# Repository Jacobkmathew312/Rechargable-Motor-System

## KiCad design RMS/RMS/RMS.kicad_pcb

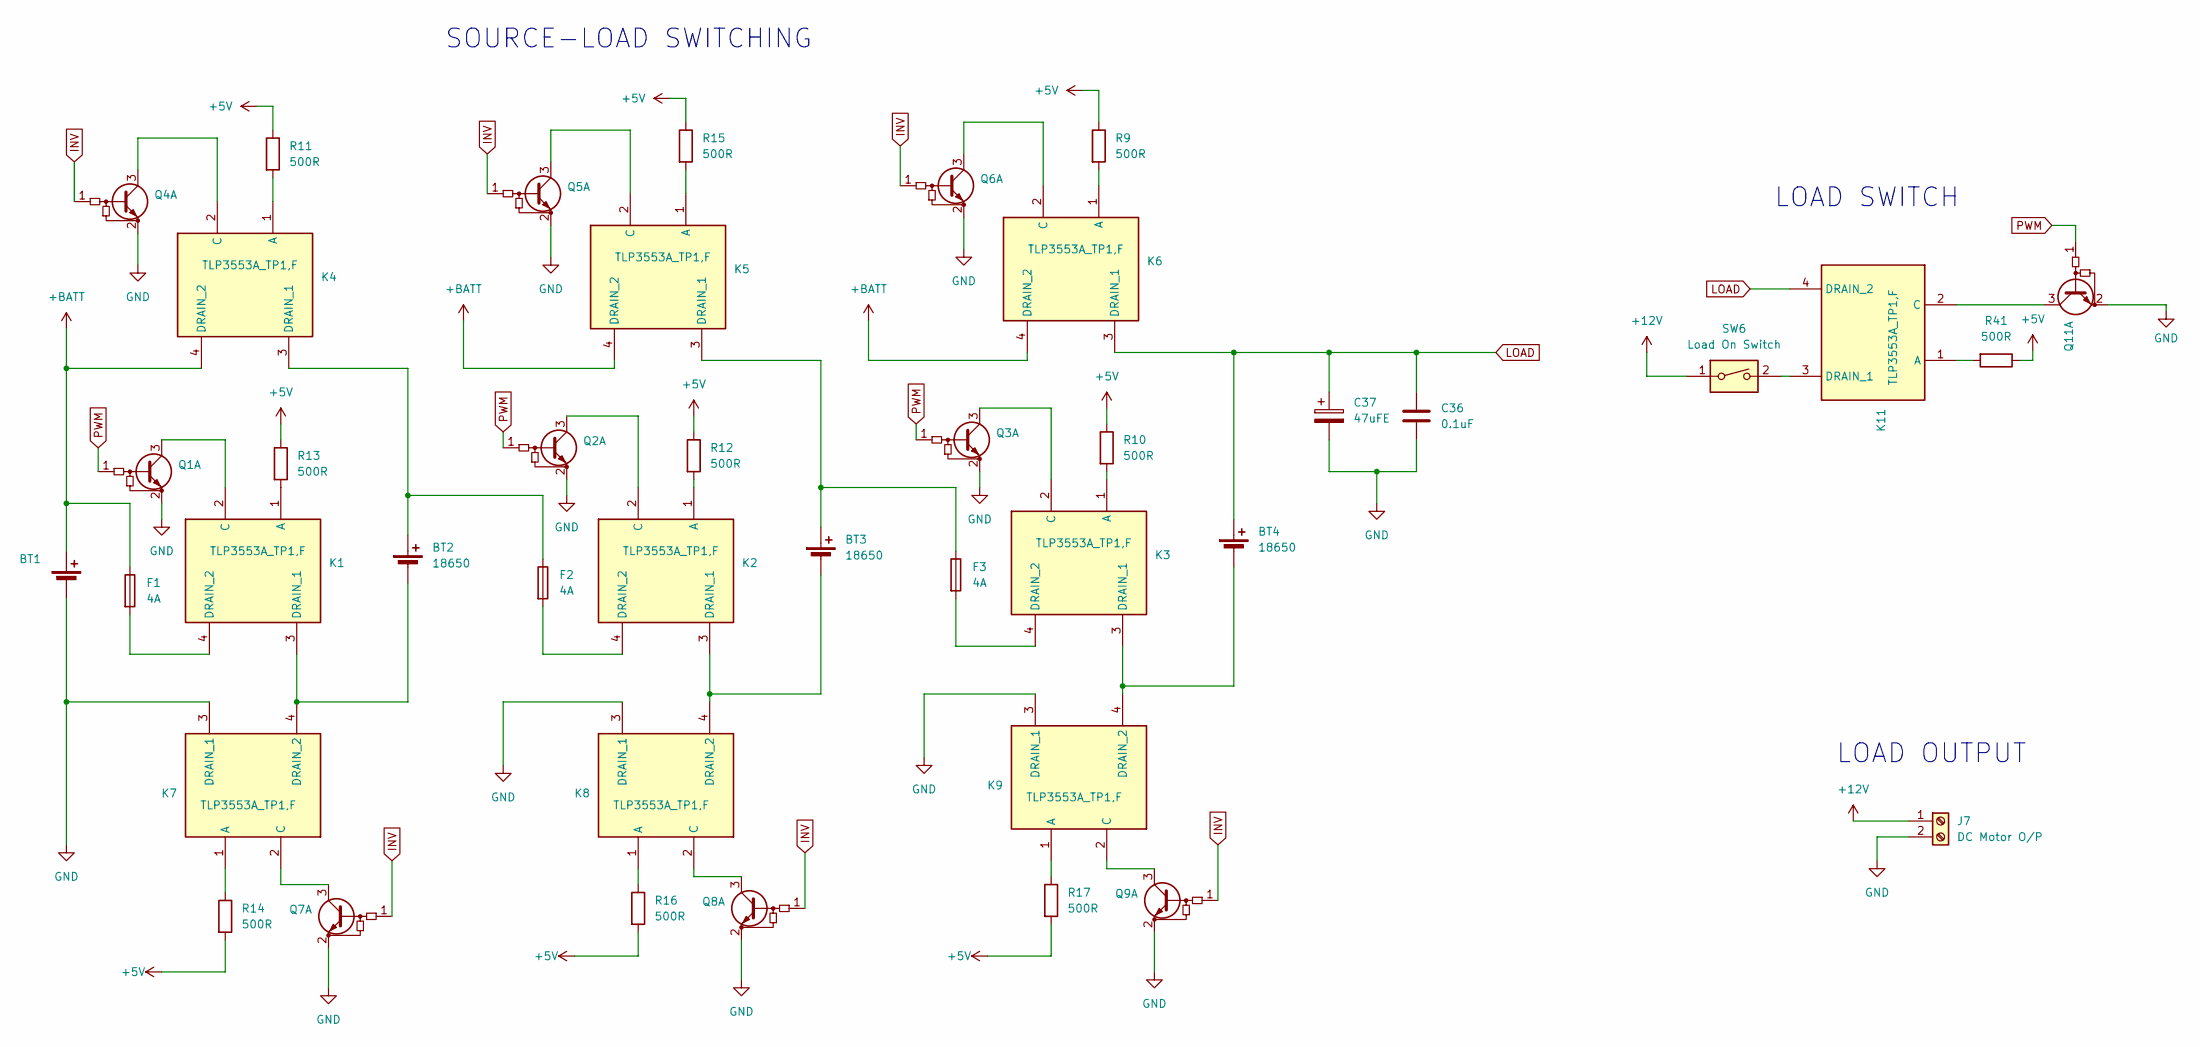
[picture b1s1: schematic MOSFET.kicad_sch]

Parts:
BT1, BT2, BT3, BT4: 18650; battery pad
C36: 0.1uF; C_0603_1608Metric
C37: 47uFE; C_Elec_6.3x5.4
F1, F2, F3: 4A; Fuse_1812_4532Metric
J7: DC Motor O/P; AMASS_XT30U-M_1x02_P5.0mm_Vertical
K1, K2, K3, K4, K5, K6, K7, K8, K9, K11: TLP3553A_TP1,F; SOIC_3553ATP1_F_TOS; Mouser Part Number 757-TLP3543ATP1F
Q1, Q2, Q3, Q4, Q5, Q6, Q7, Q8, Q9, Q11: Q_Dual_NPN_NPN_BRT_E1B1C2E2B2C1; SOT-323_SC-70
R9, R10, R11, R12, R13, R14, R15, R16, R17, R41: 500R; R_0805_2012Metric
SW6: Load On Switch; Push button

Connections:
+5V: R9.1, R10.1, R11.1, R12.1, R13.1, R14.2, R15.1, R16.2, R17.2, R41.1; also elsewhere on the board
+12V: J7.1, SW6.1; also elsewhere on the board
+BATT: BT1.1 (+), F1.1, K4.4 (DRAIN_2), K5.4 (DRAIN_2), K6.4 (DRAIN_2); also elsewhere on the board
INV: Q4.1 (B1), Q5.1 (B1), Q6.1 (B1), Q7.1 (B1), Q8.1 (B1), Q9.1 (B1); also elsewhere on the board
LOAD: BT4.1 (+), C36.1, C37.1, K6.3 (DRAIN_1), K11.4 (DRAIN_2); also elsewhere on the board
unnamed: BT2.1 (+), F2.1, K4.3 (DRAIN_1)
unnamed: BT3.1 (+), F3.1, K5.3 (DRAIN_1)
unnamed: BT3.2 (-), K2.3 (DRAIN_1), K8.4 (DRAIN_2)
unnamed: BT4.2 (-), K3.3 (DRAIN_1), K9.4 (DRAIN_2)
unnamed: K1.1 (A), R13.2
unnamed: K1.2 (C), Q1.3 (C1)
unnamed: F1.2, K1.4 (DRAIN_2)
unnamed: K2.1 (A), R12.2
unnamed: K2.2 (C), Q2.3 (C1)
unnamed: F2.2, K2.4 (DRAIN_2)
unnamed: K3.1 (A), R10.2
unnamed: K3.2 (C), Q3.3 (C1)
unnamed: F3.2, K3.4 (DRAIN_2)
unnamed: K4.2 (C), Q4.3 (C1)
unnamed: K5.1 (A), R15.2
unnamed: K5.2 (C), Q5.3 (C1)
unnamed: K6.1 (A), R9.2
unnamed: K6.2 (C), Q6.3 (C1)
unnamed: K8.1 (A), R16.1
unnamed: K8.2 (C), Q8.3 (C1)
unnamed: K9.1 (A), R17.1
unnamed: K11.1 (A), R41.2
unnamed: K11.2 (C), Q11.3 (C1)
unnamed: K11.3 (DRAIN_1), SW6.2
PWM: Q1.1 (B1), Q2.1 (B1), Q3.1 (B1), Q11.1 (B1); also elsewhere on the board

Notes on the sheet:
LOAD SWITCH
SOURCE-LOAD SWITCHING
LOAD OUTPUT

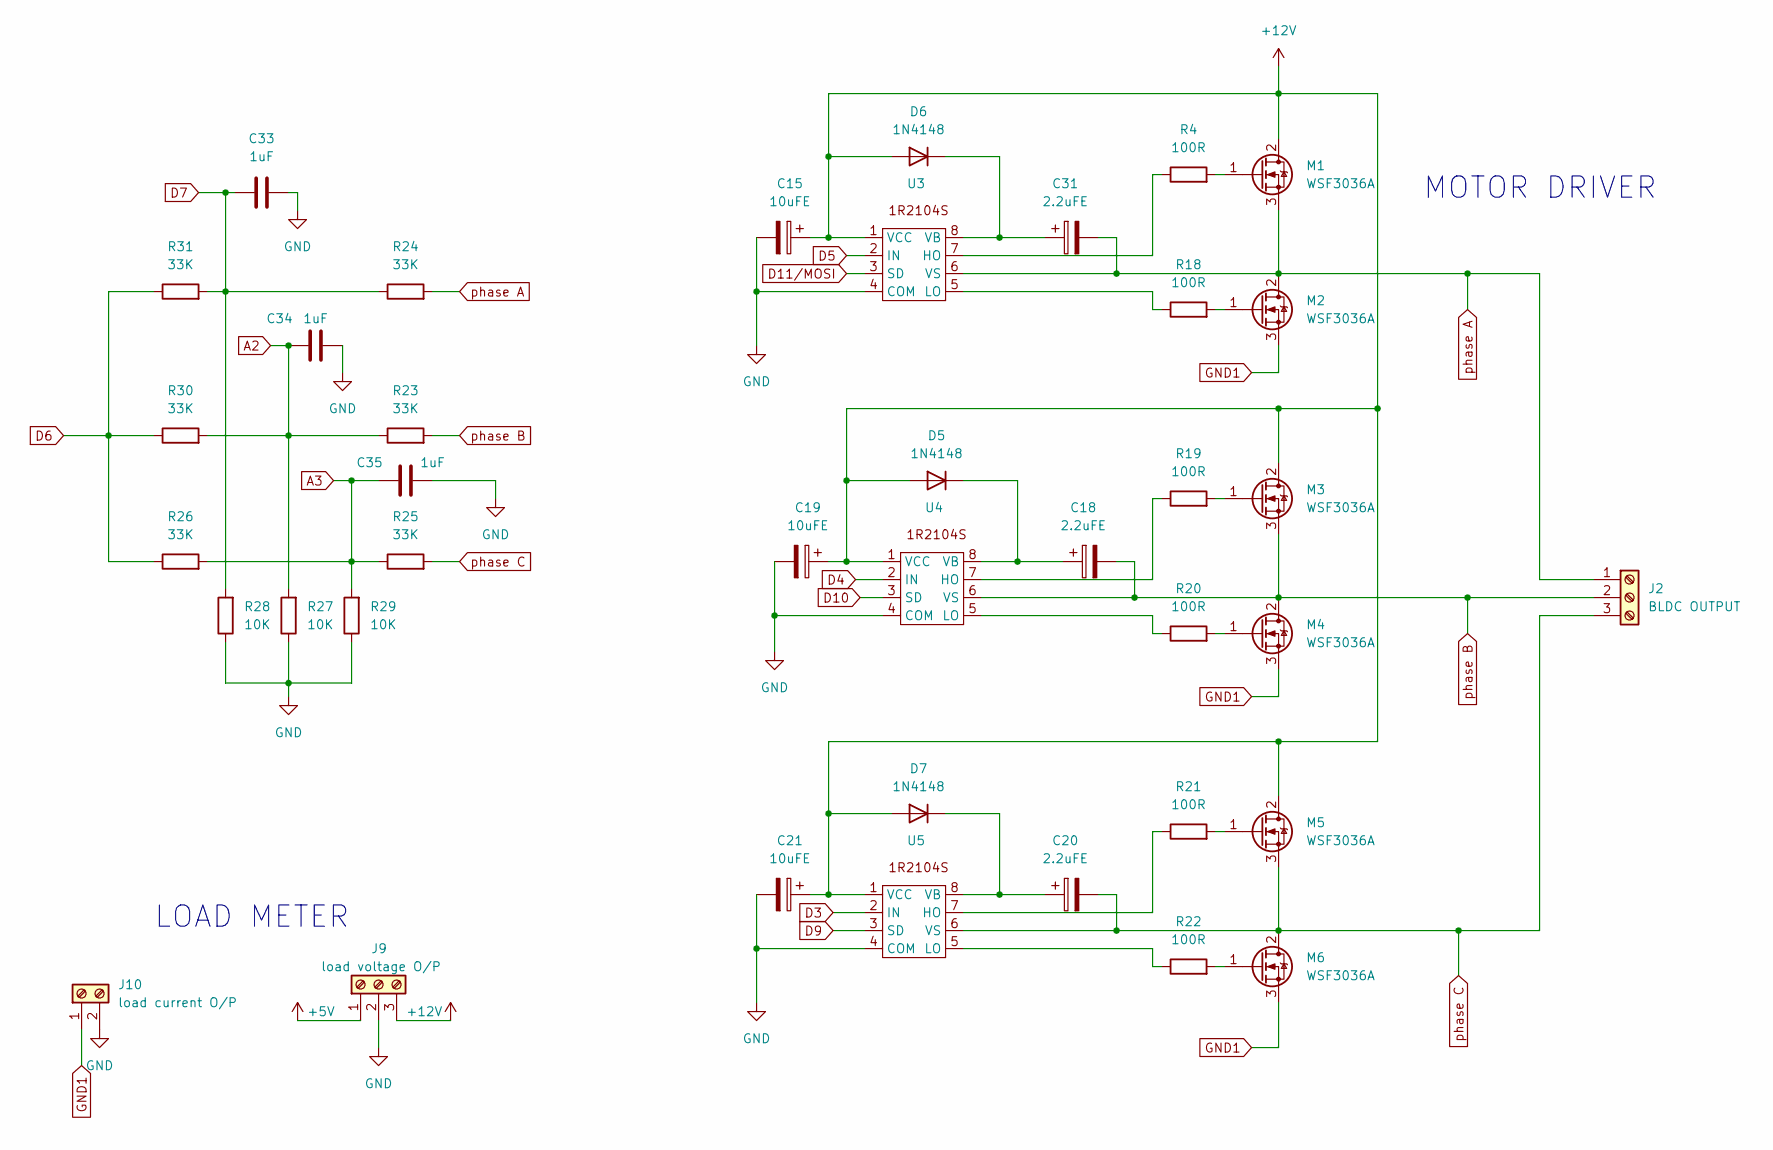
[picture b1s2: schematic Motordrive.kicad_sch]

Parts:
C15, C19, C21: 10uFE; CP_Elec_4x5.4
C18, C20, C31: 2.2uFE; C_Elec_4x5.4
C33, C34, C35: 1uF; C_0603_1608Metric
D5, D6, D7: 1N4148; D_SOD-123
J2: BLDC OUTPUT; BLDC
J9: load voltage O/P; voltage slot
J10: load current O/P; current slot
M1, M2, M3, M4, M5, M6: WSF3036A; TO-252-2
R4, R18, R19, R20, R21, R22: 100R; R_0603_1608Metric
R23, R24, R25, R26, R30, R31: 33K; R_0603_1608Metric
R27, R28, R29: 10K; R_0603_1608Metric
U3, U4, U5: SOIC-8_3.9x4.9mm_P1.27mm

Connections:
+5V: J9.1; also elsewhere on the board
+12V: C15.1, C19.1, C21.1, D5.2 (A), D6.2 (A), D7.2 (A), J9.3, M1.2 (D), M3.2 (D), M5.2 (D), U3.1 (VCC), U4.1 (VCC), U5.1 (VCC); also elsewhere on the board
A2: C34.2, R23.1, R27.2, R30.2; also elsewhere on the board
A3: C35.1, R25.1, R26.2, R29.2; also elsewhere on the board
D3: U5.2 (IN); also elsewhere on the board
D4: U4.2 (IN); also elsewhere on the board
D5: U3.2 (IN); also elsewhere on the board
D6: R26.1, R30.1, R31.1; also elsewhere on the board
D7: C33.1, R24.1, R28.2, R31.2; also elsewhere on the board
D9: U5.3 (SD); also elsewhere on the board
D10: U4.3 (SD); also elsewhere on the board
D11/MOSI: U3.3 (SD); also elsewhere on the board
GND1: J10.1, M2.3 (S), M4.3 (S), M6.3 (S)
unnamed: C18.1, D5.1 (K), U4.8 (VB)
unnamed: C31.1, D6.1 (K), U3.8 (VB)
unnamed: C20.1, D7.1 (K), U5.8 (VB)
unnamed: M1.1 (G), R4.2
unnamed: M2.1 (G), R18.2
unnamed: M3.1 (G), R19.2
unnamed: M4.1 (G), R20.2
unnamed: M5.1 (G), R21.2
unnamed: M6.1 (G), R22.2
unnamed: R4.1, U3.7 (HO)
unnamed: R18.1, U3.5 (LO)
unnamed: R19.1, U4.7 (HO)
unnamed: R20.1, U4.5 (LO)
unnamed: R21.1, U5.7 (HO)
unnamed: R22.1, U5.5 (LO)
phase A: C31.2, J2.1, M1.3 (S), M2.2 (D), R24.2, U3.6 (VS)
phase B: C18.2, J2.2, M3.3 (S), M4.2 (D), R23.2, U4.6 (VS)
phase C: C20.2, J2.3, M5.3 (S), M6.2 (D), R25.2, U5.6 (VS)

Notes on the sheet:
LOAD METER
MOTOR DRIVER

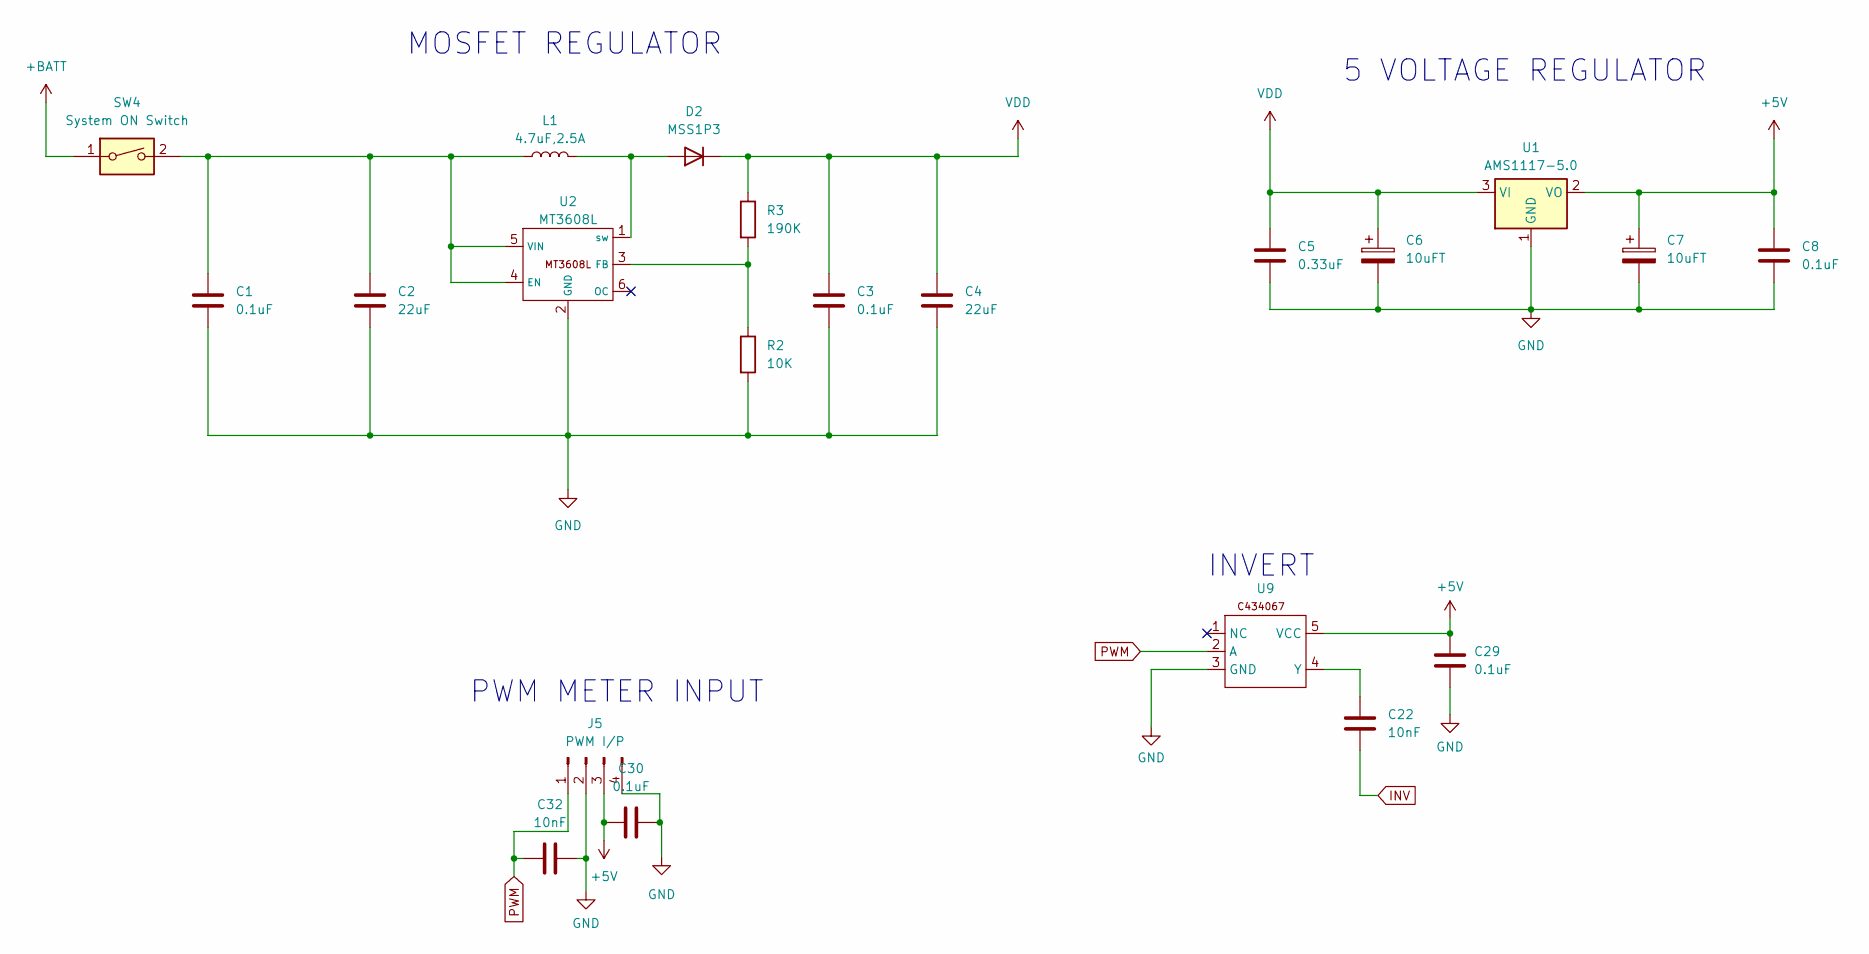
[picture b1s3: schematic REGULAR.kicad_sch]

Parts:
C1, C3, C8, C29, C30: 0.1uF; C_0603_1608Metric
C2, C4: 22uF; C_0603_1608Metric
C5: 0.33uF; C_0603_1608Metric
C6, C7: 10uFT; CP_EIA-3216-10_Kemet-I
C22, C32: 10nF; C_0603_1608Metric
D2: MSS1P3; D_MicroSMP_AK
J5: PWM I/P; PWM
L1: 4.7uF,2.5A; 4.7uH 2.5A
R2: 10K; R_0603_1608Metric
R3: 190K; R_0603_1608Metric
SW4: System ON Switch; Push button
U1: AMS1117-5.0; SOT-223-3_TabPin2
U2: MT3608L; SOT-23-6
U9: SOT-23-5

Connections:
+5V: C7.1, C8.1, C29.1, C30.1, J5.3, U1.2 (VO), U9.5 (VCC); also elsewhere on the board
+BATT: SW4.1; also elsewhere on the board
INV: C22.1; also elsewhere on the board
unnamed: D2.2 (A), L1.2, U2.1 (sw)
unnamed: C1.1, C2.1, L1.1, SW4.2, U2.4 (EN), U2.5 (VIN)
unnamed: R2.1, R3.2, U2.3 (FB)
unnamed: C22.2, U9.4 (Y)
PWM: C32.1, J5.1, U9.2 (A); also elsewhere on the board
VDD: C3.1, C4.1, C5.1, C6.1, D2.1 (K), R3.1, U1.3 (VI)

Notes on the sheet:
PWM METER INPUT
MOSFET REGULATOR
5 VOLTAGE REGULATOR
INVERT

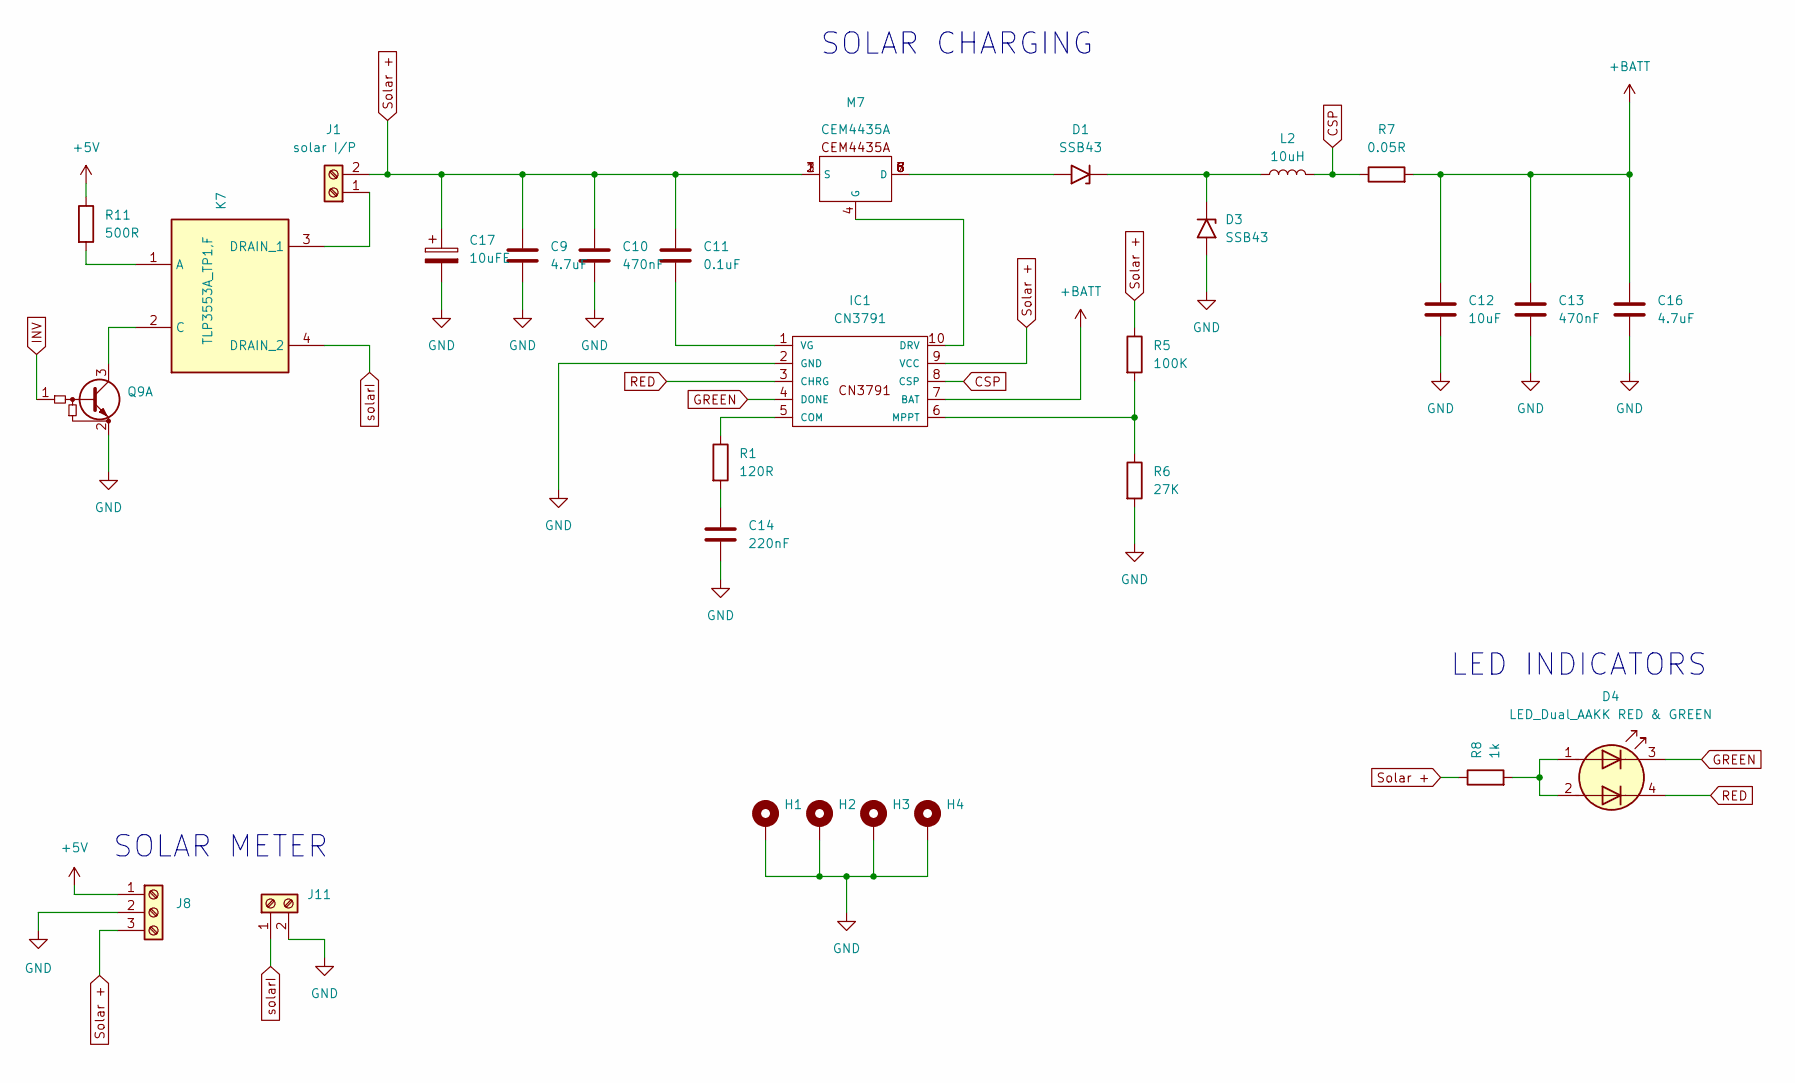
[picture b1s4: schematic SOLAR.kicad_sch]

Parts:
C9, C16: 4.7uF; C_0603_1608Metric
C10, C13: 470nF; C_0603_1608Metric
C11: 0.1uF; C_0603_1608Metric
C12: 10uF; C_0805_2012Metric
C14: 220nF; C_0603_1608Metric
C17: 10uFE; CP_Elec_4x5.4
D1, D3: SSB43; D_SMB
D4: LED_Dual_AAKK RED & GREEN; LED_SK6812_EC15_1.5x1.5mm
H1, H2, H3, H4: MountingHole_Pad; MountingHole_3.2mm_M3_Pad_Via
IC1: CN3791; SSOP10
J1: solar I/P; AMASS_XT30U-M_1x02_P5.0mm_Vertical
J8: solar voltage; voltage slot
J11: solar current; current slot
K7: TLP3553A_TP1,F; SOIC_3553ATP1_F_TOS; Mouser Part Number 757-TLP3543ATP1F
L2: 10uH
M7: CEM4435A; SOP-8_3.9x4.9mm_P1.27mm
Q9: Q_Dual_NPN_NPN_BRT_E1B1C2E2B2C1; SOT-323_SC-70
R1: 120R; R_0603_1608Metric
R5: 100K; R_0603_1608Metric
R6: 27K; R_0603_1608Metric
R7: 0.05R; R_2512_6332Metric
R8: 1k; R_0603_1608Metric
R11: 500R; R_0805_2012Metric

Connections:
+5V: J8.1, R11.1; also elsewhere on the board
+BATT: C12.1, C13.1, C16.1, IC1.7 (BAT), R7.2; also elsewhere on the board
CSP: IC1.8 (CSP), L2.2, R7.1
GREEN: D4.3 (K1), IC1.4 (DONE)
INV: Q9.1 (B1); also elsewhere on the board
unnamed: C14.1, R1.2
unnamed: D1.1 (A1), D3.1 (A1), L2.1
unnamed: D1.2 (A2), M7.5 (D), M7.6 (D), M7.7 (D), M7.8 (D)
unnamed: D4.1 (A1), D4.2 (A2), R8.2
unnamed: IC1.5 (COM), R1.1
unnamed: IC1.10 (DRV), M7.4 (G)
unnamed: IC1.6 (MPPT), R5.2, R6.1
unnamed: C11.2, IC1.1 (VG)
RED: D4.4 (K2), IC1.3 (CHRG)
Solar +: C9.1, C10.1, C11.1, C17.1, IC1.9 (VCC), J1.2, J8.3, M7.1 (S), M7.2 (S), M7.3 (S), R5.1, R8.1

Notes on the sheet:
SOLAR CHARGING
LED INDICATORS
SOLAR METER

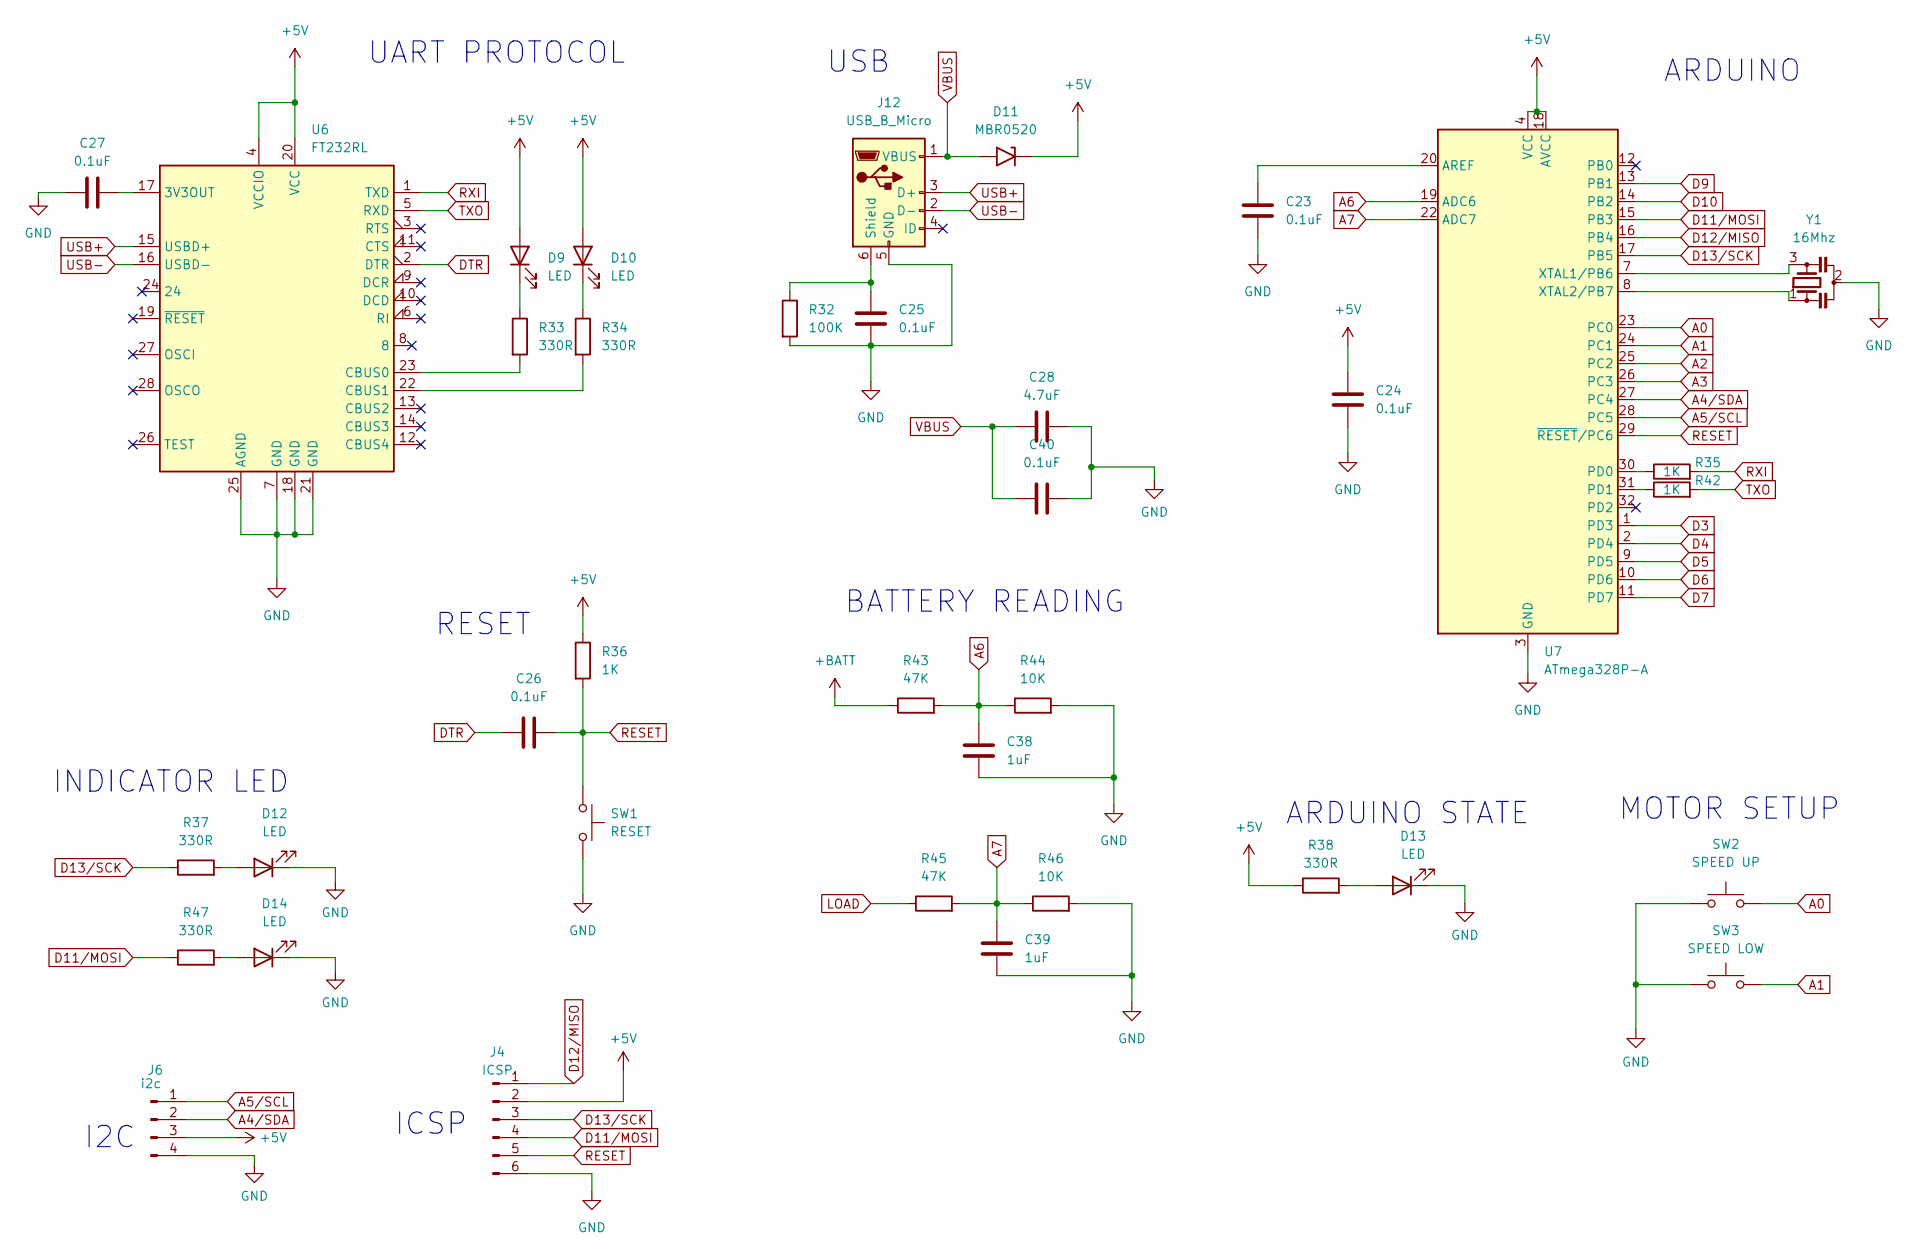
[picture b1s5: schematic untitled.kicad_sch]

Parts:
C23, C24, C25, C26, C27, C40: 0.1uF; C_0603_1608Metric
C28: 4.7uF; C_0603_1608Metric
C38, C39: 1uF; C_0603_1608Metric
D9, D10, D12, D13, D14: LED; LED_0603_1608Metric
D11: MBR0520; D_SOD-123
J4: ICSP; PinHeader_2x03_P2.54mm_Vertical
J6: i2c; PinHeader_1x04_P2.54mm_Vertical
J12: USB_B_Micro; USB_Micro-B_XKB_U254-051T-4BH83-F1S
R32: 100K; R_0603_1608Metric
R33, R34, R37, R38, R47: 330R; R_0603_1608Metric
R35, R36, R42: 1K; R_0603_1608Metric
R43, R45: 47K; R_0603_1608Metric
R44, R46: 10K; R_0603_1608Metric
SW1: RESET; SW_SPST_FSMSM
SW2: SPEED UP; SW_Push_1P1T_NO_6x6mm_H9.5mm
SW3: SPEED LOW; SW_Push_1P1T_NO_6x6mm_H9.5mm
U6: FT232RL; SSOP-28_5.3x10.2mm_P0.65mm
U7: ATmega328P-A; TQFP-32_7x7mm_P0.8mm
Y1: 16Mhz; Resonator_SMD_Murata_CSTxExxV-3Pin_3.0x1.1mm

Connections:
+5V: C24.1, D9.2 (A), D10.2 (A), D11.1 (A1), J4.2, J6.3, R36.1, R38.1, U6.4 (VCCIO), U6.20 (VCC), U7.4 (VCC), U7.6 (VCC), U7.18 (AVCC); also elsewhere on the board
+BATT: R43.1; also elsewhere on the board
A0: SW2.2, U7.23 (PC0)
A1: SW3.2, U7.24 (PC1)
A2: U7.25 (PC2); also elsewhere on the board
A3: U7.26 (PC3); also elsewhere on the board
A4/SDA: J6.2, U7.27 (PC4)
A5/SCL: J6.1, U7.28 (PC5)
A6: C38.1, R43.2, R44.1, U7.19 (ADC6)
A7: C39.1, R45.2, R46.1, U7.22 (ADC7)
D3: U7.1 (PD3); also elsewhere on the board
D4: U7.2 (PD4); also elsewhere on the board
D5: U7.9 (PD5); also elsewhere on the board
D6: U7.10 (PD6); also elsewhere on the board
D7: U7.11 (PD7); also elsewhere on the board
D9: U7.13 (PB1); also elsewhere on the board
D10: U7.14 (PB2); also elsewhere on the board
D11/MOSI: J4.4, R47.1, U7.15 (PB3); also elsewhere on the board
D12/MISO: J4.1, U7.16 (PB4)
D13/SCK: J4.3, R37.1, U7.17 (PB5)
DTR: C26.1, U6.2 (DTR)
LOAD: R45.1; also elsewhere on the board
unnamed: D9.1 (K), R33.1
unnamed: D10.1 (K), R34.1
unnamed: D12.2 (A), R37.2
unnamed: D13.2 (A), R38.2
unnamed: D14.2 (A), R47.2
unnamed: C25.1, J12.6 (Shield), R32.1
unnamed: C27.2, U6.17 (3V3OUT)
unnamed: R33.2, U6.23 (CBUS0)
unnamed: R34.2, U6.22 (CBUS1)
unnamed: C23.2, U7.20 (AREF)
unnamed: R35.1, U7.30 (PD0)
unnamed: R42.1, U7.31 (PD1)
unnamed: U7.7 (XTAL1/PB6), Y1.3
unnamed: U7.8 (XTAL2/PB7), Y1.1
RESET: C26.2, J4.5, R36.2, SW1.2, U7.29 (~RESET/PC6)
RXI: R35.2, U6.1 (TXD)
TXO: R42.2, U6.5 (RXD)
USB+: J12.3 (D+), U6.15 (USBD+)
USB-: J12.2 (D-), U6.16 (USBD-)
VBUS: C28.1, C40.1, D11.2 (A2), J12.1 (VBUS)

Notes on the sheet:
ARDUINO
I2C
UART PROTOCOL
RESET
MOTOR SETUP
ICSP
USB
BATTERY READING
INDICATOR LED
ARDUINO STATE

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
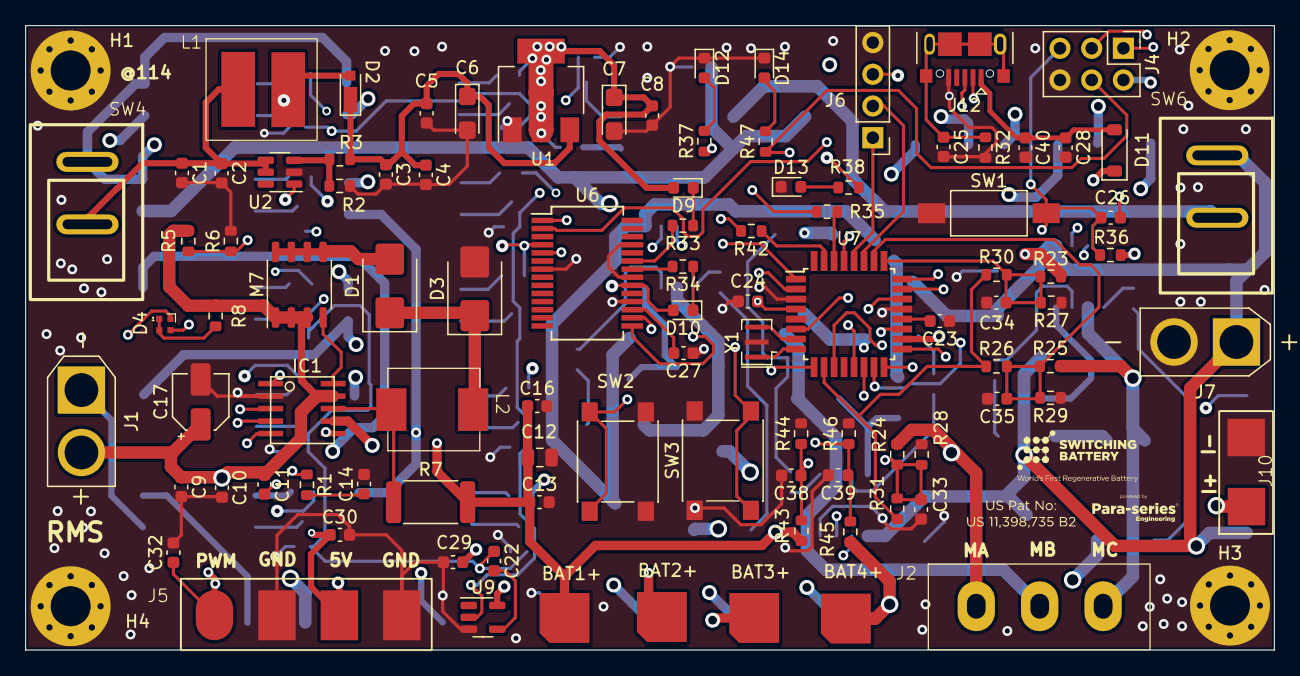
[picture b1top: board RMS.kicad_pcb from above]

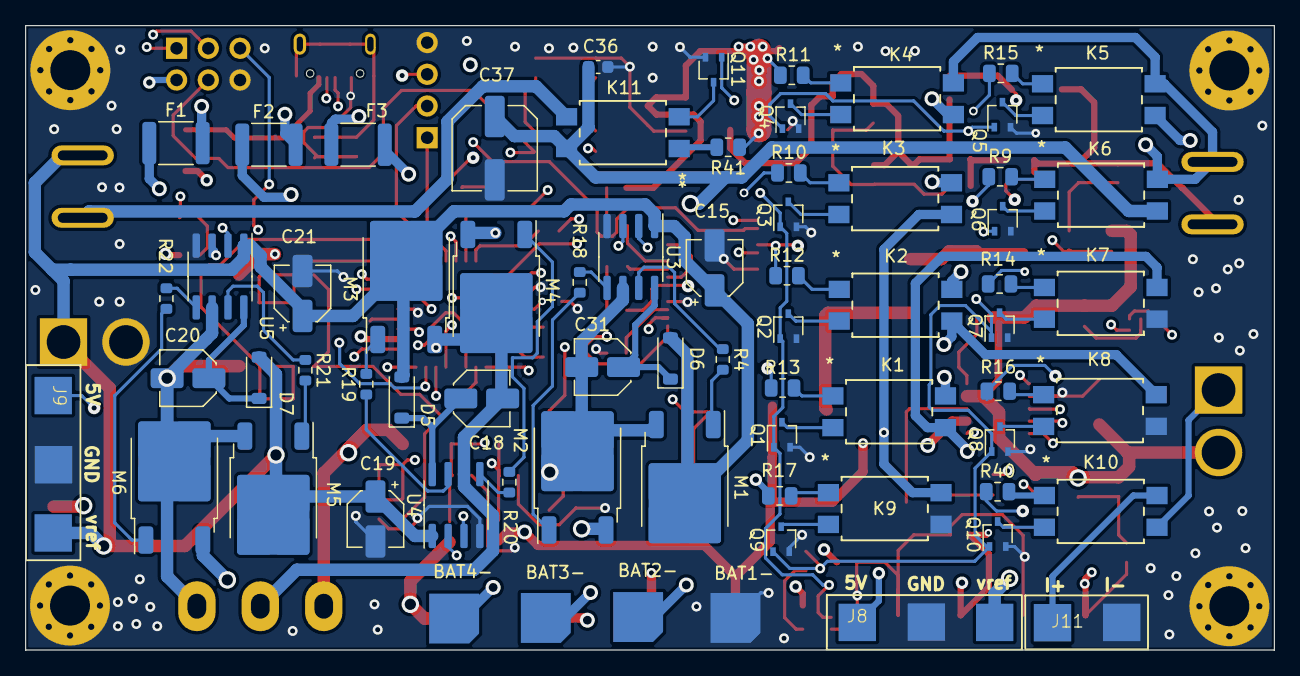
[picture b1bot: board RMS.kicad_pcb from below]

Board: 6 copper layers, 100.0 x 50.0 mm, 167 parts (65 on the bottom side), 115 nets.

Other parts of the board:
K10: TLP3553A_TP1,F; SOIC_3553ATP1_F_TOS
Q10: Q_Dual_NPN_NPN_BRT_E1B1C2E2B2C1; SOT-323_SC-70
R40: 500R; R_0805_2012Metric

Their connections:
+5V: R40.1; also elsewhere on the board
INV: Q10.1 (B1); also elsewhere on the board
unnamed: K10.1 (A), R40.2
unnamed: K10.2 (C), Q10.3 (C1)

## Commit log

2025-03-13 13-03-25
    initial commit
